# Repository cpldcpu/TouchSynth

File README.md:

# TouchSynth

A small MCU-controlled analog monophonic synthesizer on a 100 × 100 mm, 4-layer PCB. It has no
potentiometers and no mechanical switches: 13 capacitive touch keys plus SHIFT / − / + play and edit it, and
16 LEDs show the settings. A CH32V003 (or CH32V002 / V006) generates the oscillator timing and four
PWM control voltages for a discrete analog voice:

- **DCO:** a TL072 integrator reset by the MCU timer. The charge current tracks pitch, so the saw amplitude
  stays flat. Saw, variable-width pulse, sub-oscillator and noise.
- **VCF:** a 24 dB/oct transistor ladder (BC847BS) with an expo converter and resonance up to self-oscillation.
- **VCA:** a differential-pair VCA. An 8-bit R-2R trim DAC nulls the CV feedthrough ("thump").
- **Line out,** an audio loopback into the MCU ADC (for calibration and tests), and an optional MIDI in.

All assembled parts are JLCPCB **Basic** or **Promotional Extended** parts: 40 BOM lines, 196 placements,
about USD 3.65 of parts per board at list price. The MCU, headers and MIDI parts are hand-soldered.

**Status (2026-10-18):** board 1 (rev 0.1, CH32V006) is built and brought up. It passes the bring-up steps
and functional tests T1, T2 and T4–T12 (noise marginal at about −55 dB); T3 (touch scan rate) and T14 (MIDI)
have not been measured. The results are in the
[design report](docs/report/touchsynth_report.pdf), section 10. Firmware 0.1 runs on the board, including
multitrack demo pieces and percussion presets. Calibration storage in flash is still open.

The `polyphonic_exp` branch experiments with extensions. So far it turns the pulse output into a PWM DAC
(CH32V006) for digital voices through the analog filter and VCA, starting with a modal timpani, the *kettle*
([kettle_model.mp3](docs/audio/pieces/kettle_model.mp3); report, section 10.5).

Design: cpldcpu & Claude Opus 5.5.

## Hear it

Recorded from board 1's line out. The synth is monophonic, so the multitrack pieces were played one part at a
time and mixed:

| Piece | Board 1 | Model |
|---|---|---|
| *TouchSynth Demo*, original, 7 parts (drums, acid bass, arp, lead, pad) | [demo_hw](docs/audio/demo/touchsynth_demo_hw.mp3) | [demo_model](docs/audio/demo/touchsynth_demo_model.mp3) |
| Purcell, *Queen Mary's March*: 4 trumpets, bass, timpani (modal synthesis on the PWM DAC) | [march_hw](docs/audio/pieces/march_hw.mp3) | [march_model](docs/audio/pieces/march_model.mp3) |
| Bach, Toccata BWV 565, mm. 1–30: 9 organ voices | [toccata_hw](docs/audio/pieces/toccata_hw.mp3) | [toccata_model](docs/audio/pieces/toccata_model.mp3) |
| *Aerosphere*, original space-synth piece, 8 parts | [aero_hw](docs/audio/pieces/aero_hw.mp3) | [aero_model](docs/audio/pieces/aero_model.mp3) |
| Suite: Aerosphere intro into the Toccata | [suite_hw](docs/audio/pieces/suite_hw.mp3) | [suite_model](docs/audio/pieces/suite_model.mp3) |

The three built-in demo tunes (SHIFT + C' on the board), recorded from board 1:
[acid](docs/audio/hw_board1/tune_acid.mp3), [prelude](docs/audio/hw_board1/tune_prelude.mp3) (Bach BWV 846) and
[ode](docs/audio/hw_board1/tune_ode.mp3) (Beethoven). Also from the board: a
[waveform tour](docs/audio/hw_board1/waveforms.mp3) and a [scale on the self-oscillating filter](docs/audio/hw_board1/selfosc_scale.mp3).
The behavioural model renders every single feature (waveforms, filter, envelopes, glide, …) in
[docs/audio/features/](docs/audio/features/). [docs/README.md](docs/README.md) lists all audio files.

## Documents

| Document | Content |
|---|---|
| [docs/report/touchsynth_report.pdf](docs/report/touchsynth_report.pdf) | **design report**: requirements, architecture, circuits, simulations, PCB, BOM, firmware, demo tunes and instruments, V&V with the board 1 results |
| [docs/README.md](docs/README.md) | index of everything in `docs/`: documents, figures, result data, audio |
| [docs/spec.md](docs/spec.md) | specification and design decisions (some pre-layout details are outdated; the report is current) |
| [docs/sim_report.md](docs/sim_report.md) | simulation report S1–S7 and the behavioural model |
| [docs/verification_plan.md](docs/verification_plan.md) | bring-up, functional tests, calibration and validation, board 1 results |
| [docs/touchsynth_schematic.pdf](docs/touchsynth_schematic.pdf) | schematic (7 sheets) |
| [firmware/touchsynth/README.md](firmware/touchsynth/README.md) | firmware build, playing instructions and test console |
| [hw/README.md](hw/README.md) | schematic generator scripts |

## Repository layout

```
docs/        report (LaTeX), spec, simulation report, V&V plan, figures, audio examples, result CSVs
sim/         ngspice simulations S1–S7 (one folder per block), shared netlists and models, behavioural model
hw/          design.py (single source of truth) -> KiCad schematic, PCB, routing and fab outputs
  touchsynth/  KiCad 10 project (generated; edit the Python sources, not the KiCad files)
firmware/    touchsynth/ firmware 0.1, ch32fun (git submodule)
parts/       JLCPCB Basic / Promotional Extended part lists
tools/       bench tools: hardware tests, scope recording, multitrack mixing, figures; Freerouting jar (not in git)
```

## Flow

Every stage is generated by scripts from [hw/design.py](hw/design.py), which holds the parts, values, LCSC
numbers and nets.

```
simulate      sim/s*/s*.py                 ngspice-42 in WSL -> docs/results/*.csv, docs/figures/*.png
model         sim/behav/validate.py        behavioural model vs. ngspice
              sim/behav/examples.py        audio examples + spectrograms
schematic     hw/gen_sch2.py               -> hw/touchsynth/*.kicad_sch
              hw/check_netlist.py          KiCad netlist == design.py
              hw/check_sim.py              design.py == simulation netlists
PCB           hw/gen_pcb.py [--route]      placement, silkscreen art, planes, Freerouting + GND stitching
              hw/gen_pcb.py --finish       post-route clean-up (islands, leftovers via the A* router)
fab           hw/fab.py                    gerbers, drill, BOM and CPL -> hw/touchsynth/production/
report        docs/report/gen_tables.py    then: latexmk -pdf touchsynth_report.tex (WSL)
firmware      firmware/touchsynth/gen_tables.py, check_pins.py, make
tunes         sim/behav/tunes.py, pieces.py    demo tunes, multitrack pieces and presets (-> firmware tables)
bench         tools/hwtest.py              functional tests over the SWIO console -> docs/results/hw_board1*
              tools/hw_figures.py          board 1 figures for the report
              tools/record_parts.sh        record one multitrack part per take with the scope (on the lab PC)
              tools/mix_parts.py, suite.py align, clock-correct and mix the takes -> docs/audio/
```

The bench tools need the lab setup (the PC with the programmer, the scope address) in `tools/lab.conf`: copy
[tools/lab.conf.example](tools/lab.conf.example) and edit it; `lab.conf` is not in git.

`gen_pcb.py` needs KiCad's bundled Python (`pcbnew`) and Java 17 for Freerouting 1.9.0. The hw scripts find KiCad 10
in its standard install folder, or in `KICAD_DIR` if set. The other Python
scripts use a normal Python 3 with numpy and matplotlib. ngspice, LaTeX and the RISC-V toolchain run in WSL.

## Key numbers

| | |
|---|---|
| Supply | 9–12 V DC, about 31 mA (simulated); board 1: 25 mA, MCU running, LEDs off |
| Pitch range | C1 … C8, saw amplitude flat within ±2.2 % |
| Filter | 20 Hz … 20 kHz cutoff, −23 dB/oct, self-oscillation |
| VCA | 121 dB off-attenuation, thump < 0.6 mV after trim |
| Output | about 1.2 Vpp line level, AC-coupled |
| Control | 4 × 12-bit CV (10-bit PWM at 46.9 kHz + 2-bit dither), 1 kHz envelope / LFO rate |
| Touch | 16 pads via 2 × CD4051, 1.4 kHz scan |
| PCB | 100 × 100 mm, 4 layers (signal / GND / split power / signal), 242 parts, 166 nets |

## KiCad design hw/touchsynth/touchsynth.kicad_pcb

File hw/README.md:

# TouchSynth hardware (KiCad 10)

Everything here is generated from Python; edit the sources, not the `.kicad_sch` files.

| File | Role |
|---|---|
| `design.py` | single source of truth: parts (value, footprint, LCSC, sim name), nets, sheets, groups |
| `lcsc.py` | picks JLCPCB basic / promotional parts for passives (voltage rating >= 2x working voltage) |
| `layouts.py` | hand-drawn sheet layouts (placement + wires) |
| `draw.py` | drawing layer: geometric connectivity, auto-labels for split nets, short detection, junctions |
| `gen_sch2.py` | writes the schematic (`touchsynth/*.kicad_sch`) — **use this one** |
| `gen_sch.py` | v1 generator (label-only layout); its writer functions are reused by v2 |
| `check_netlist.py` | exports the KiCad netlist and compares it with `design.py` |
| `check_sim.py` | compares the design with the ngspice netlists (S6 + S7) |
| `touchsynth/TouchSynth.pretty` | touch-key footprints (copper under solder mask) |

```
python gen_sch2.py && kicad-cli sch erc touchsynth/touchsynth.kicad_sch && python check_netlist.py && python check_sim.py
```

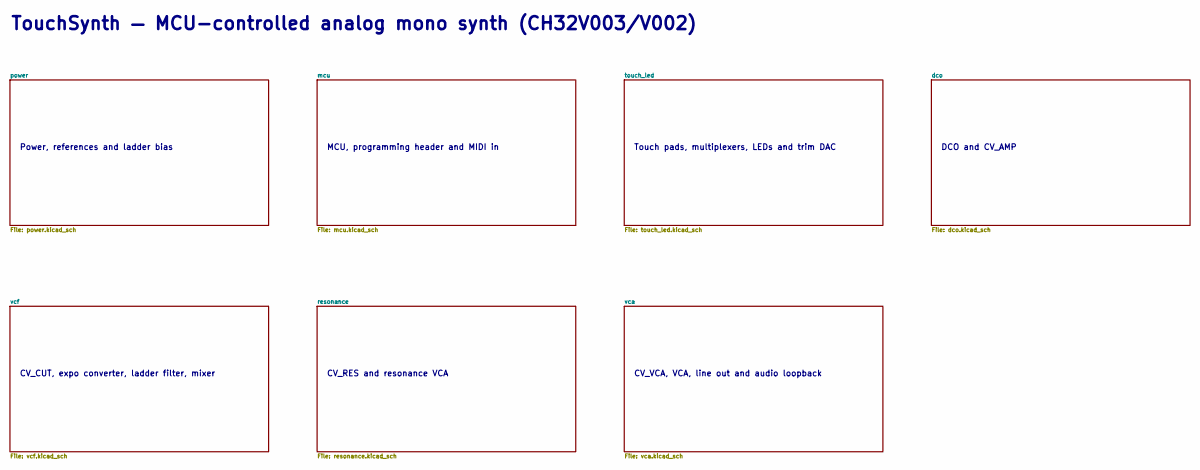
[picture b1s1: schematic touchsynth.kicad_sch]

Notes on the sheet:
Power, references and ladder bias
MCU, programming header and MIDI in
Touch pads, multiplexers, LEDs and trim DAC
DCO and CV_AMP
CV_CUT, expo converter, ladder filter, mixer
CV_RES and resonance VCA
CV_VCA, VCA, line out and audio loopback
TouchSynth — MCU-controlled analog mono synth (CH32V003/V002)

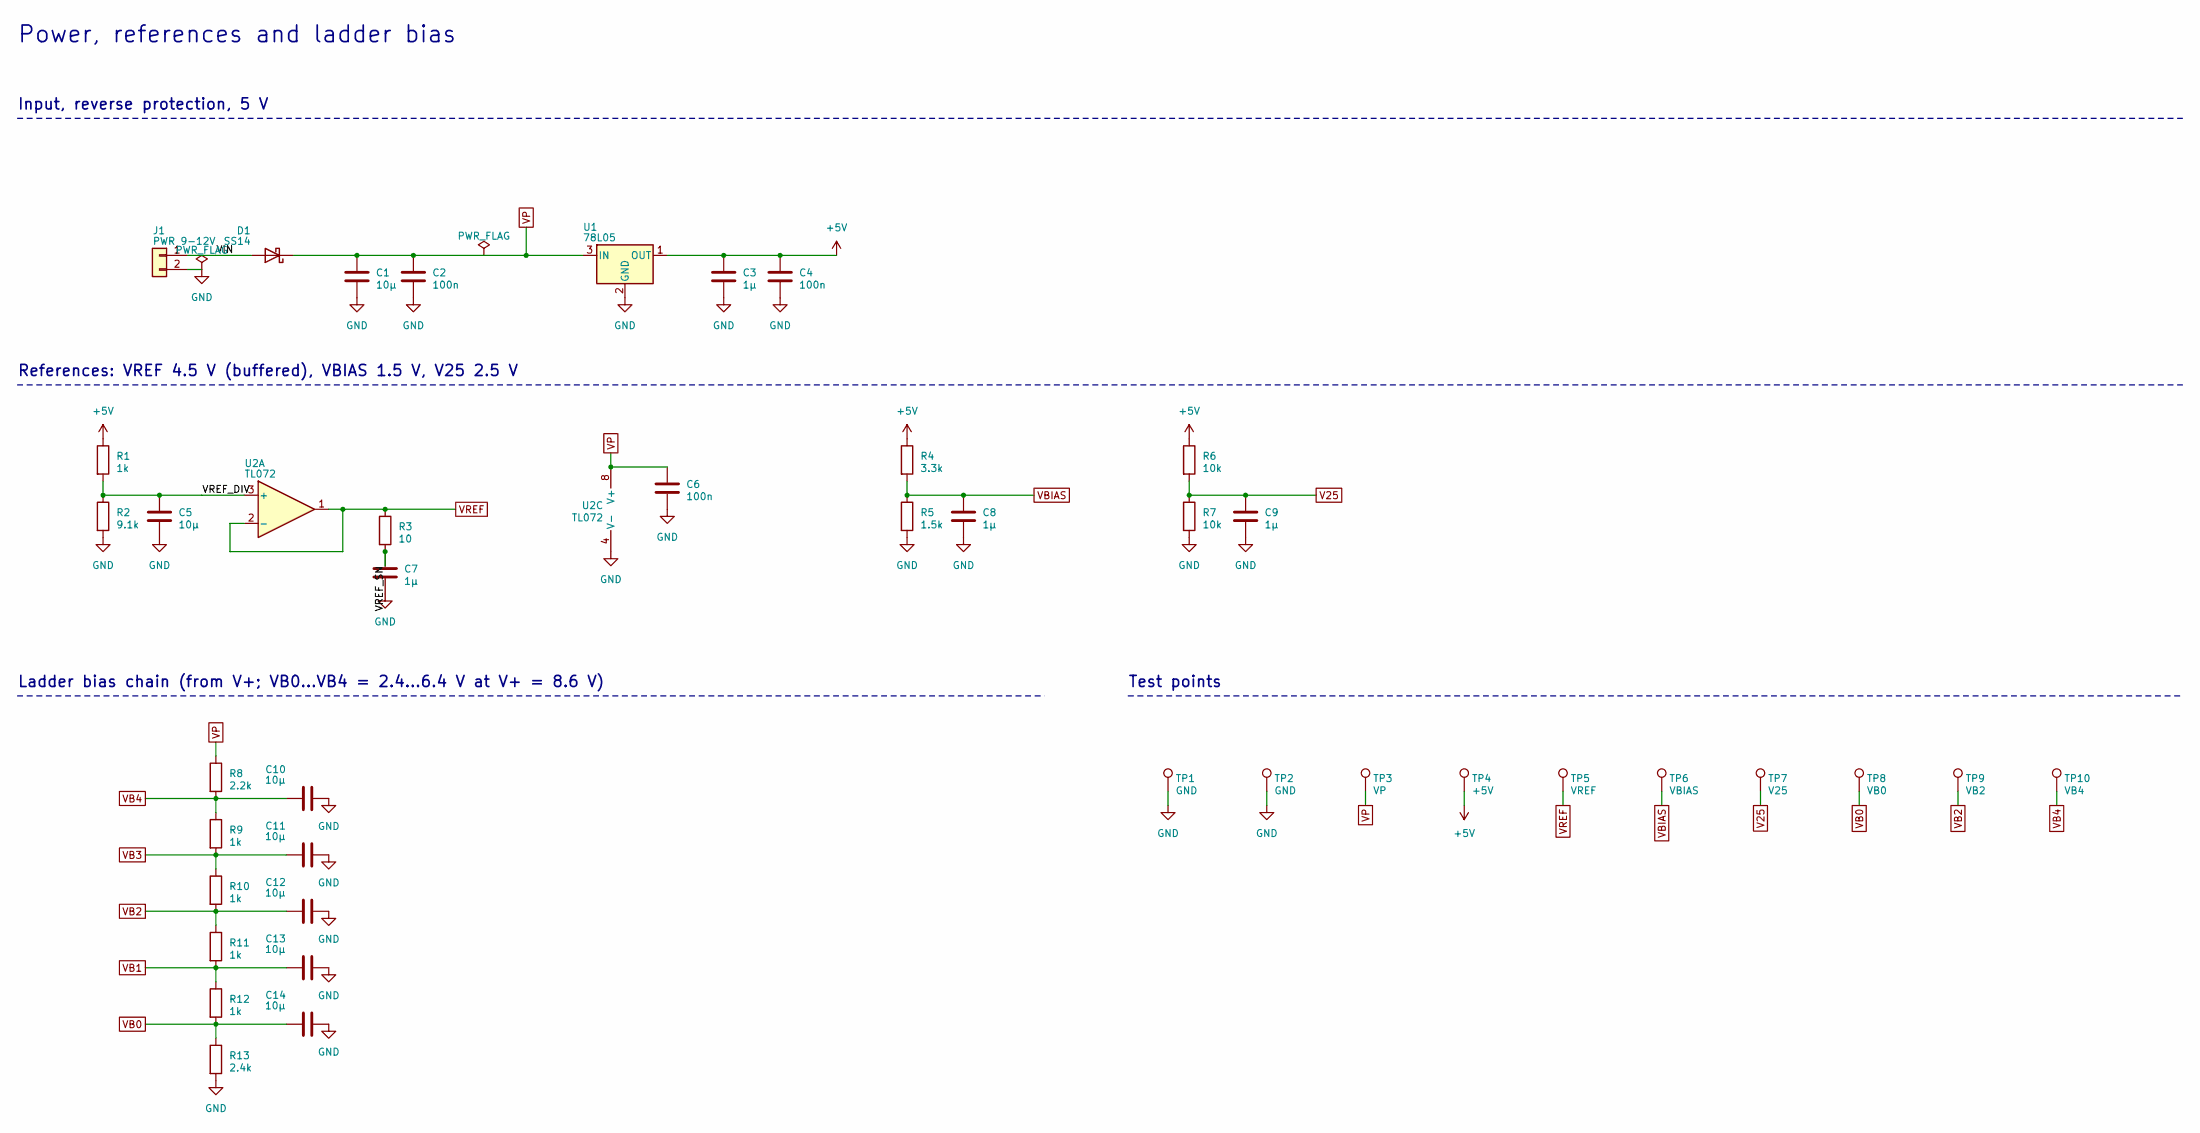
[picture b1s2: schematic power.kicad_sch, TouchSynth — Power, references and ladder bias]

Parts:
C1, C10, C11, C12, C13: 10µ; C_0603_1608Metric; LCSC C96446
C2, C4, C6: 100n; C_0603_1608Metric; LCSC C14663
C3, C7, C8, C9: 1µ; C_0603_1608Metric; LCSC C15849
C5, C14: 10µ; C_0603_1608Metric; LCSC C19702
D1: SS14; D_SMA; LCSC C2480
J1: PWR 9-12V; PinHeader_1x02_P2.54mm_Vertical
R1, R9, R10, R11, R12: 1k; R_0603_1608Metric; LCSC C21190
R2: 9.1k; R_0603_1608Metric; LCSC C23260
R3: 10; R_0603_1608Metric; LCSC C22859
R4: 3.3k; R_0603_1608Metric; LCSC C22978
R5: 1.5k; R_0603_1608Metric; LCSC C22843
R6, R7: 10k; R_0603_1608Metric; LCSC C25804
R8: 2.2k; R_0603_1608Metric; LCSC C4190
R13: 2.4k; R_0603_1608Metric; LCSC C22940
TP1, TP2: GND; PinHeader_1x01_P2.54mm_Vertical
TP3: VP; TestPoint_Pad_D1.0mm
TP4: +5V; TestPoint_Pad_D1.0mm
TP5: VREF; TestPoint_Pad_D1.0mm
TP6: VBIAS; TestPoint_Pad_D1.0mm
TP7: V25; TestPoint_Pad_D1.0mm
TP8: VB0; TestPoint_Pad_D1.0mm
TP9: VB2; TestPoint_Pad_D1.0mm
TP10: VB4; TestPoint_Pad_D1.0mm
U1: 78L05; SOT-89-3; LCSC C71136
U2: TL072; SOIC-8_3.9x4.9mm_P1.27mm; LCSC C6961

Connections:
+5V: C3.1, C4.1, R1.1, R4.1, R6.1, TP4.1, U1.1 (OUT); also elsewhere on the board
/power/VIN: D1.2 (A), J1.1
/power/VREF_DIV: C5.1, R1.2, R2.1, U2.3 (+)
/power/VREF_SN: C7.1, R3.2
GND: C1.2, C2.2, C3.2, C4.2, C5.2, C6.2, C7.2, C8.2, C9.2, C10.2, C11.2, C12.2, C13.2, C14.2, J1.2, R2.2, R5.2, R7.2, R13.2, TP1.1, TP2.1, U1.2 (GND), U2.4 (V-); also elsewhere on the board
V25: C9.1, R6.2, R7.1, TP7.1; also elsewhere on the board
VB0: C14.1, R12.2, R13.1, TP8.1; also elsewhere on the board
VB1: C13.1, R11.2, R12.1; also elsewhere on the board
VB2: C12.1, R10.2, R11.1, TP9.1; also elsewhere on the board
VB3: C11.1, R9.2, R10.1; also elsewhere on the board
VB4: C10.1, R8.2, R9.1, TP10.1; also elsewhere on the board
VBIAS: C8.1, R4.2, R5.1, TP6.1; also elsewhere on the board
VP: C1.1, C2.1, C6.1, D1.1 (K), R8.1, TP3.1, U1.3 (IN), U2.8 (V+); also elsewhere on the board
VREF: R3.1, TP5.1, U2.1, U2.2 (-); also elsewhere on the board

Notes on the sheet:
Power, references and ladder bias
Input, reverse protection, 5 V
References: VREF 4.5 V (buffered), VBIAS 1.5 V, V25 2.5 V
Ladder bias chain (from V+; VB0...VB4 = 2.4...6.4 V at V+ = 8.6 V)
Test points

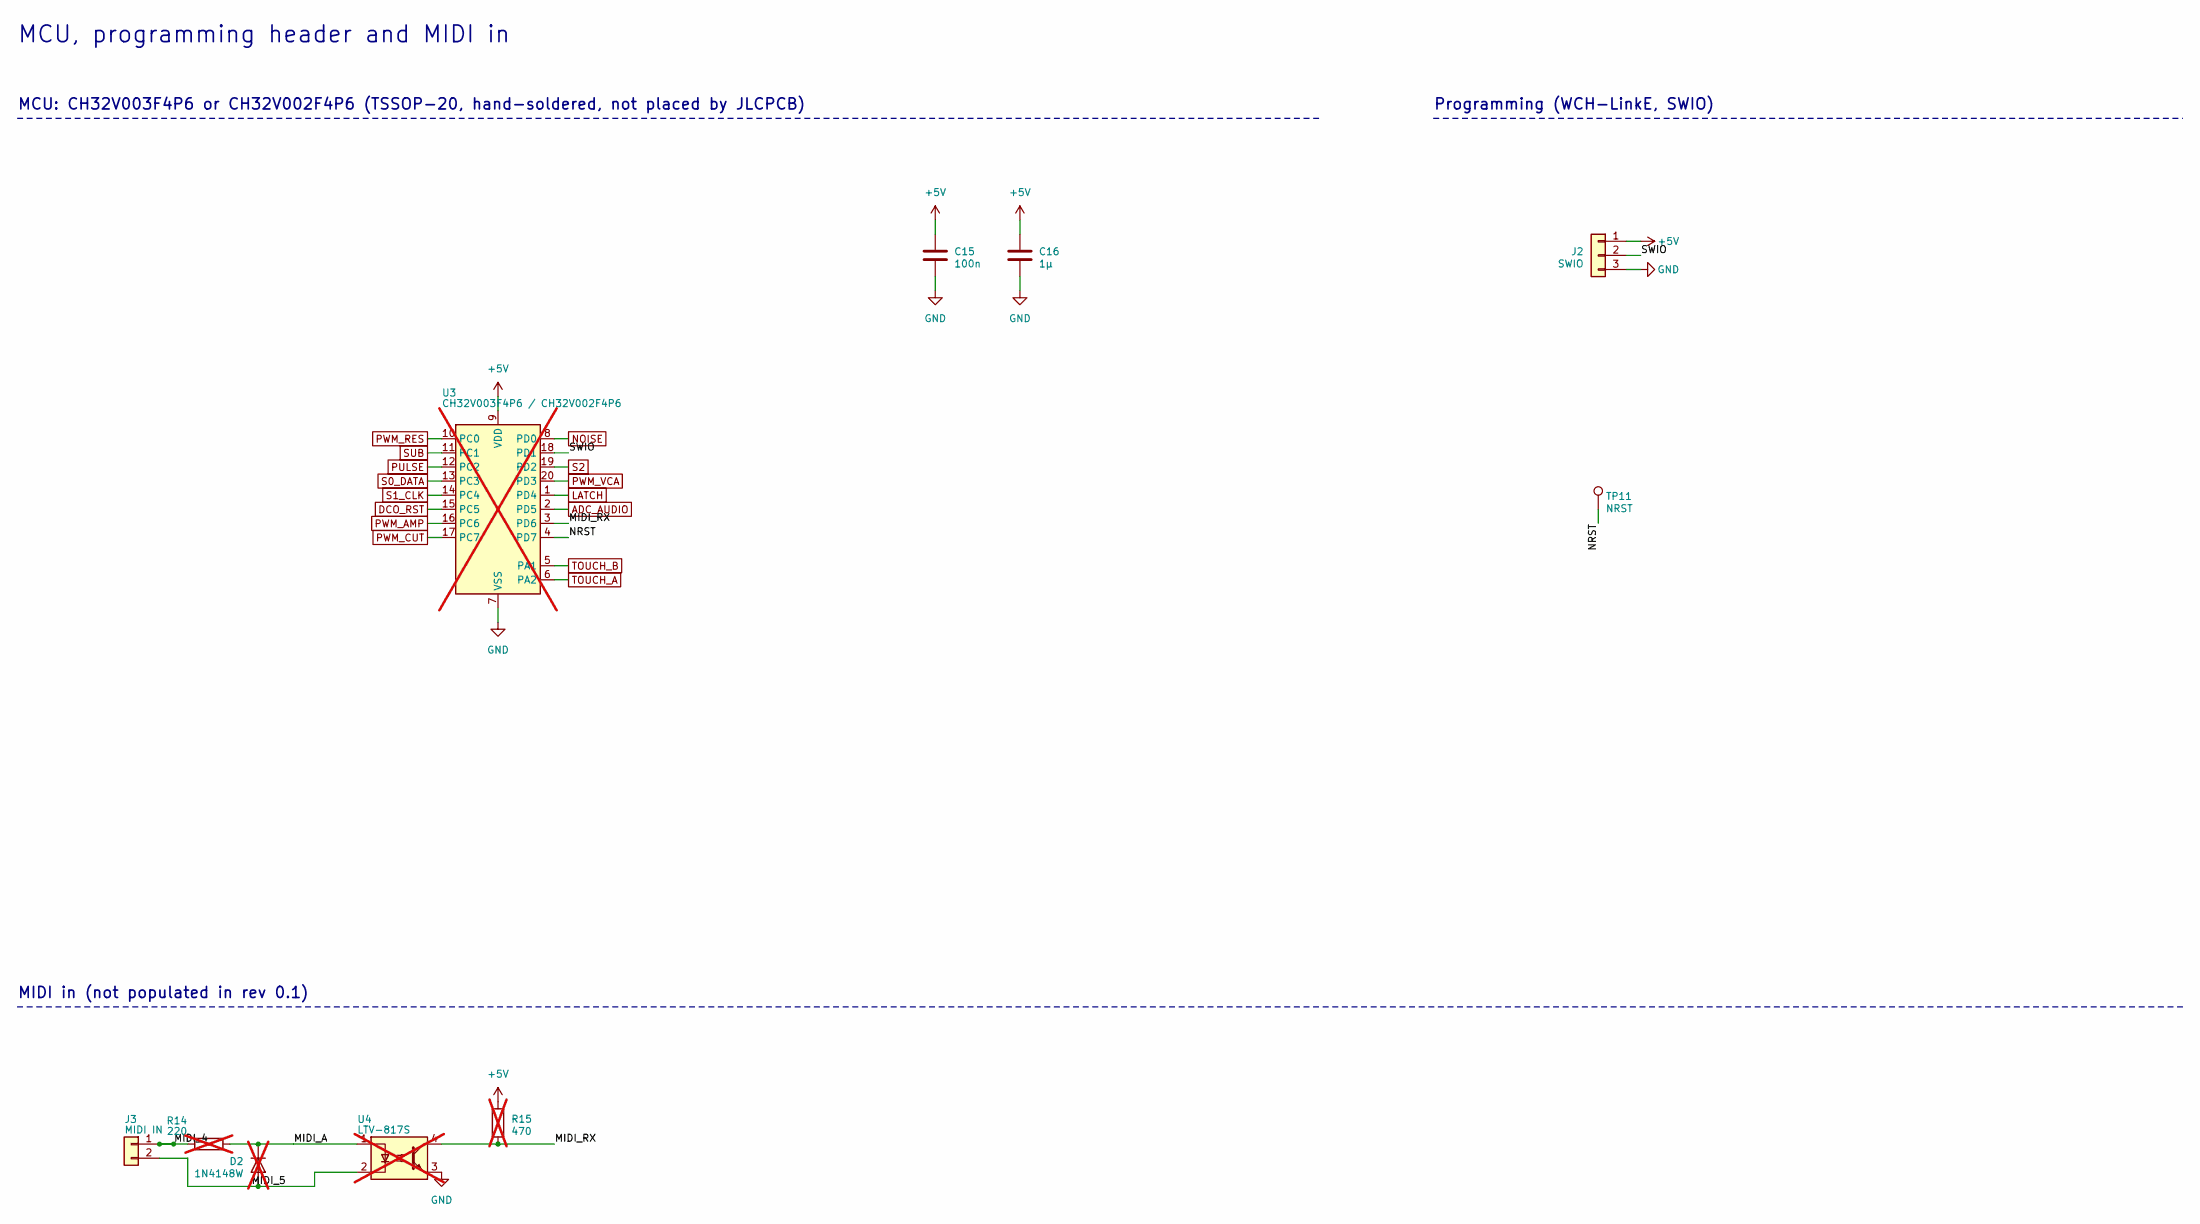
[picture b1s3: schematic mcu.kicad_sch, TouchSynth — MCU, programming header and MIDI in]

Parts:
C15: 100n; C_0603_1608Metric; LCSC C14663
C16: 1µ; C_0603_1608Metric; LCSC C15849
D2: 1N4148W; D_SOD-123; LCSC C81598; not fitted
J2: SWIO; PinHeader_1x03_P2.54mm_Vertical
J3: MIDI IN; PinHeader_1x02_P2.54mm_Vertical
R14: 220; R_0603_1608Metric; LCSC C22962; not fitted
R15: 470; R_0603_1608Metric; LCSC C23179; not fitted
TP11: NRST; TestPoint_Pad_D1.0mm
U3: CH32V003F4P6 / CH32V002F4P6; TSSOP-20_4.4x6.5mm_P0.65mm; not fitted
U4: LTV-817S; SMDIP-4_W9.53mm; LCSC C109227; not fitted

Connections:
+5V: C15.1, C16.1, J2.1, R15.1, U3.9 (VDD); also elsewhere on the board
/mcu/MIDI_4: J3.1, R14.1
/mcu/MIDI_5: D2.2 (A), J3.2, U4.2
/mcu/MIDI_A: D2.1 (K), R14.2, U4.1
/mcu/MIDI_RX: R15.2, U3.3 (PD6), U4.4
/mcu/NRST: TP11.1, U3.4 (PD7)
/mcu/SWIO: J2.2, U3.18 (PD1)
ADC_AUDIO: U3.2 (PD5); also elsewhere on the board
DCO_RST: U3.15 (PC5); also elsewhere on the board
GND: C15.2, C16.2, J2.3, U3.7 (VSS), U4.3; also elsewhere on the board
LATCH: U3.1 (PD4); also elsewhere on the board
NOISE: U3.8 (PD0); also elsewhere on the board
PULSE: U3.12 (PC2); also elsewhere on the board
PWM_AMP: U3.16 (PC6); also elsewhere on the board
PWM_CUT: U3.17 (PC7); also elsewhere on the board
PWM_RES: U3.10 (PC0); also elsewhere on the board
PWM_VCA: U3.20 (PD3); also elsewhere on the board
S0_DATA: U3.13 (PC3); also elsewhere on the board
S1_CLK: U3.14 (PC4); also elsewhere on the board
S2: U3.19 (PD2); also elsewhere on the board
SUB: U3.11 (PC1); also elsewhere on the board
TOUCH_A: U3.6 (PA2); also elsewhere on the board
TOUCH_B: U3.5 (PA1); also elsewhere on the board

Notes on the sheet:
MCU, programming header and MIDI in
MCU: CH32V003F4P6 or CH32V002F4P6 (TSSOP-20, hand-soldered, not placed by JLCPCB)
Programming (WCH-LinkE, SWIO)
MIDI in (not populated in rev 0.1)

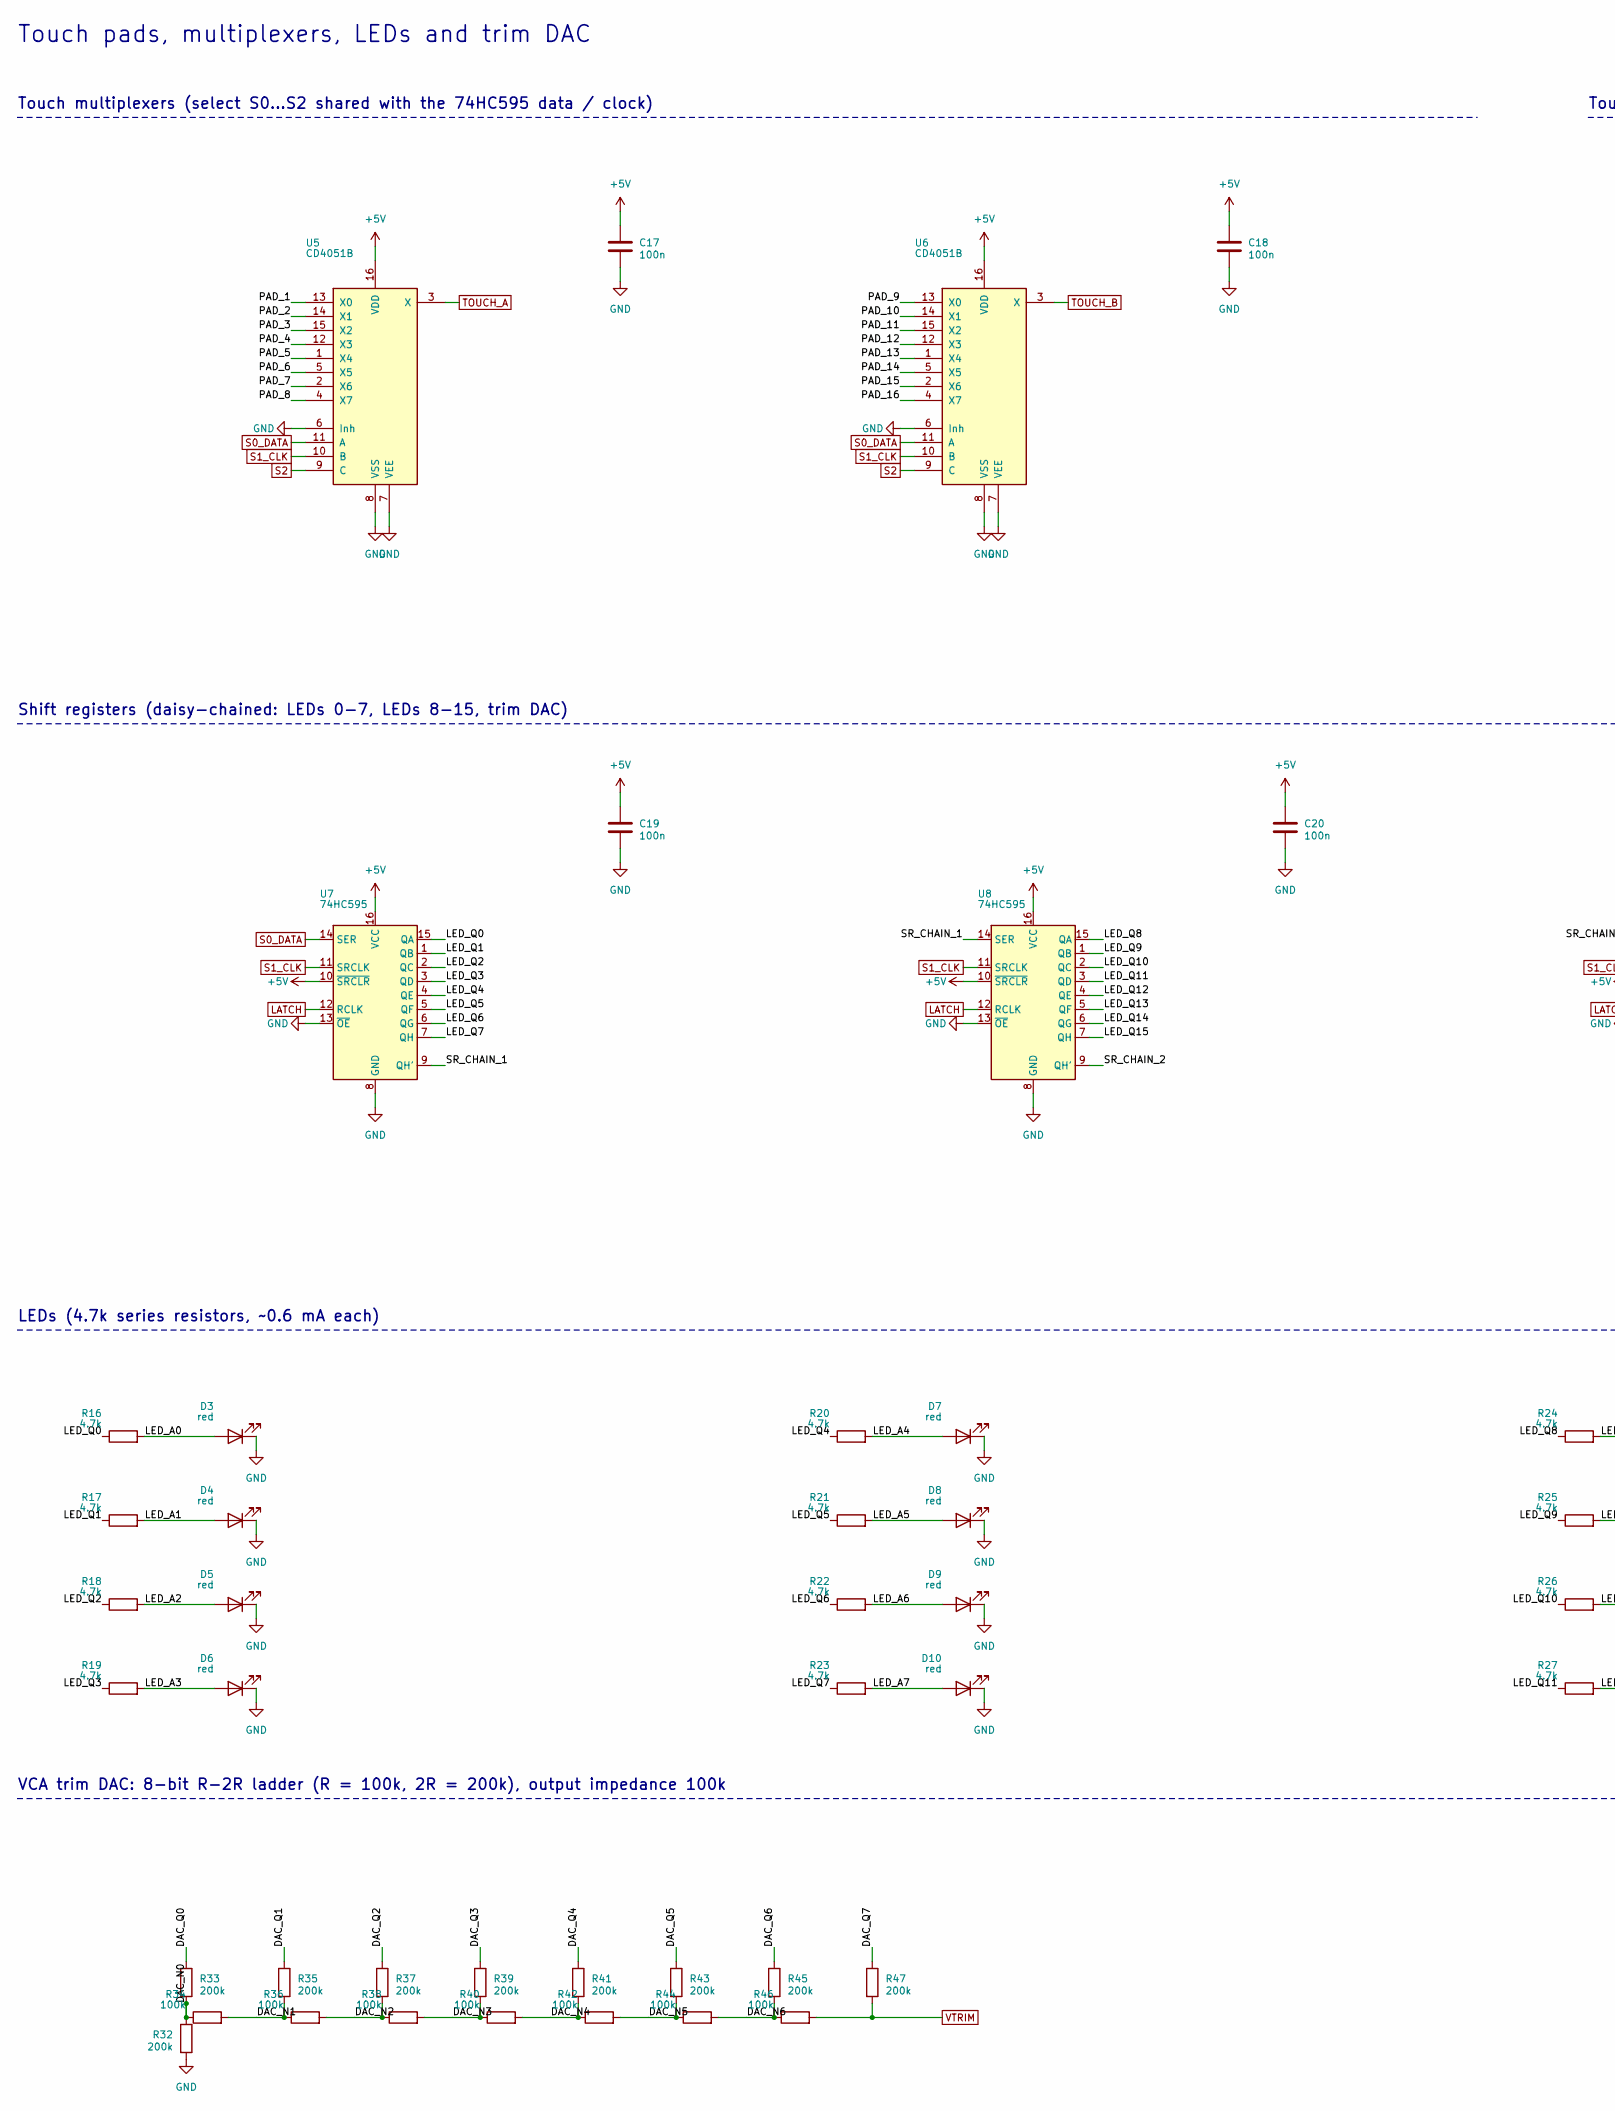
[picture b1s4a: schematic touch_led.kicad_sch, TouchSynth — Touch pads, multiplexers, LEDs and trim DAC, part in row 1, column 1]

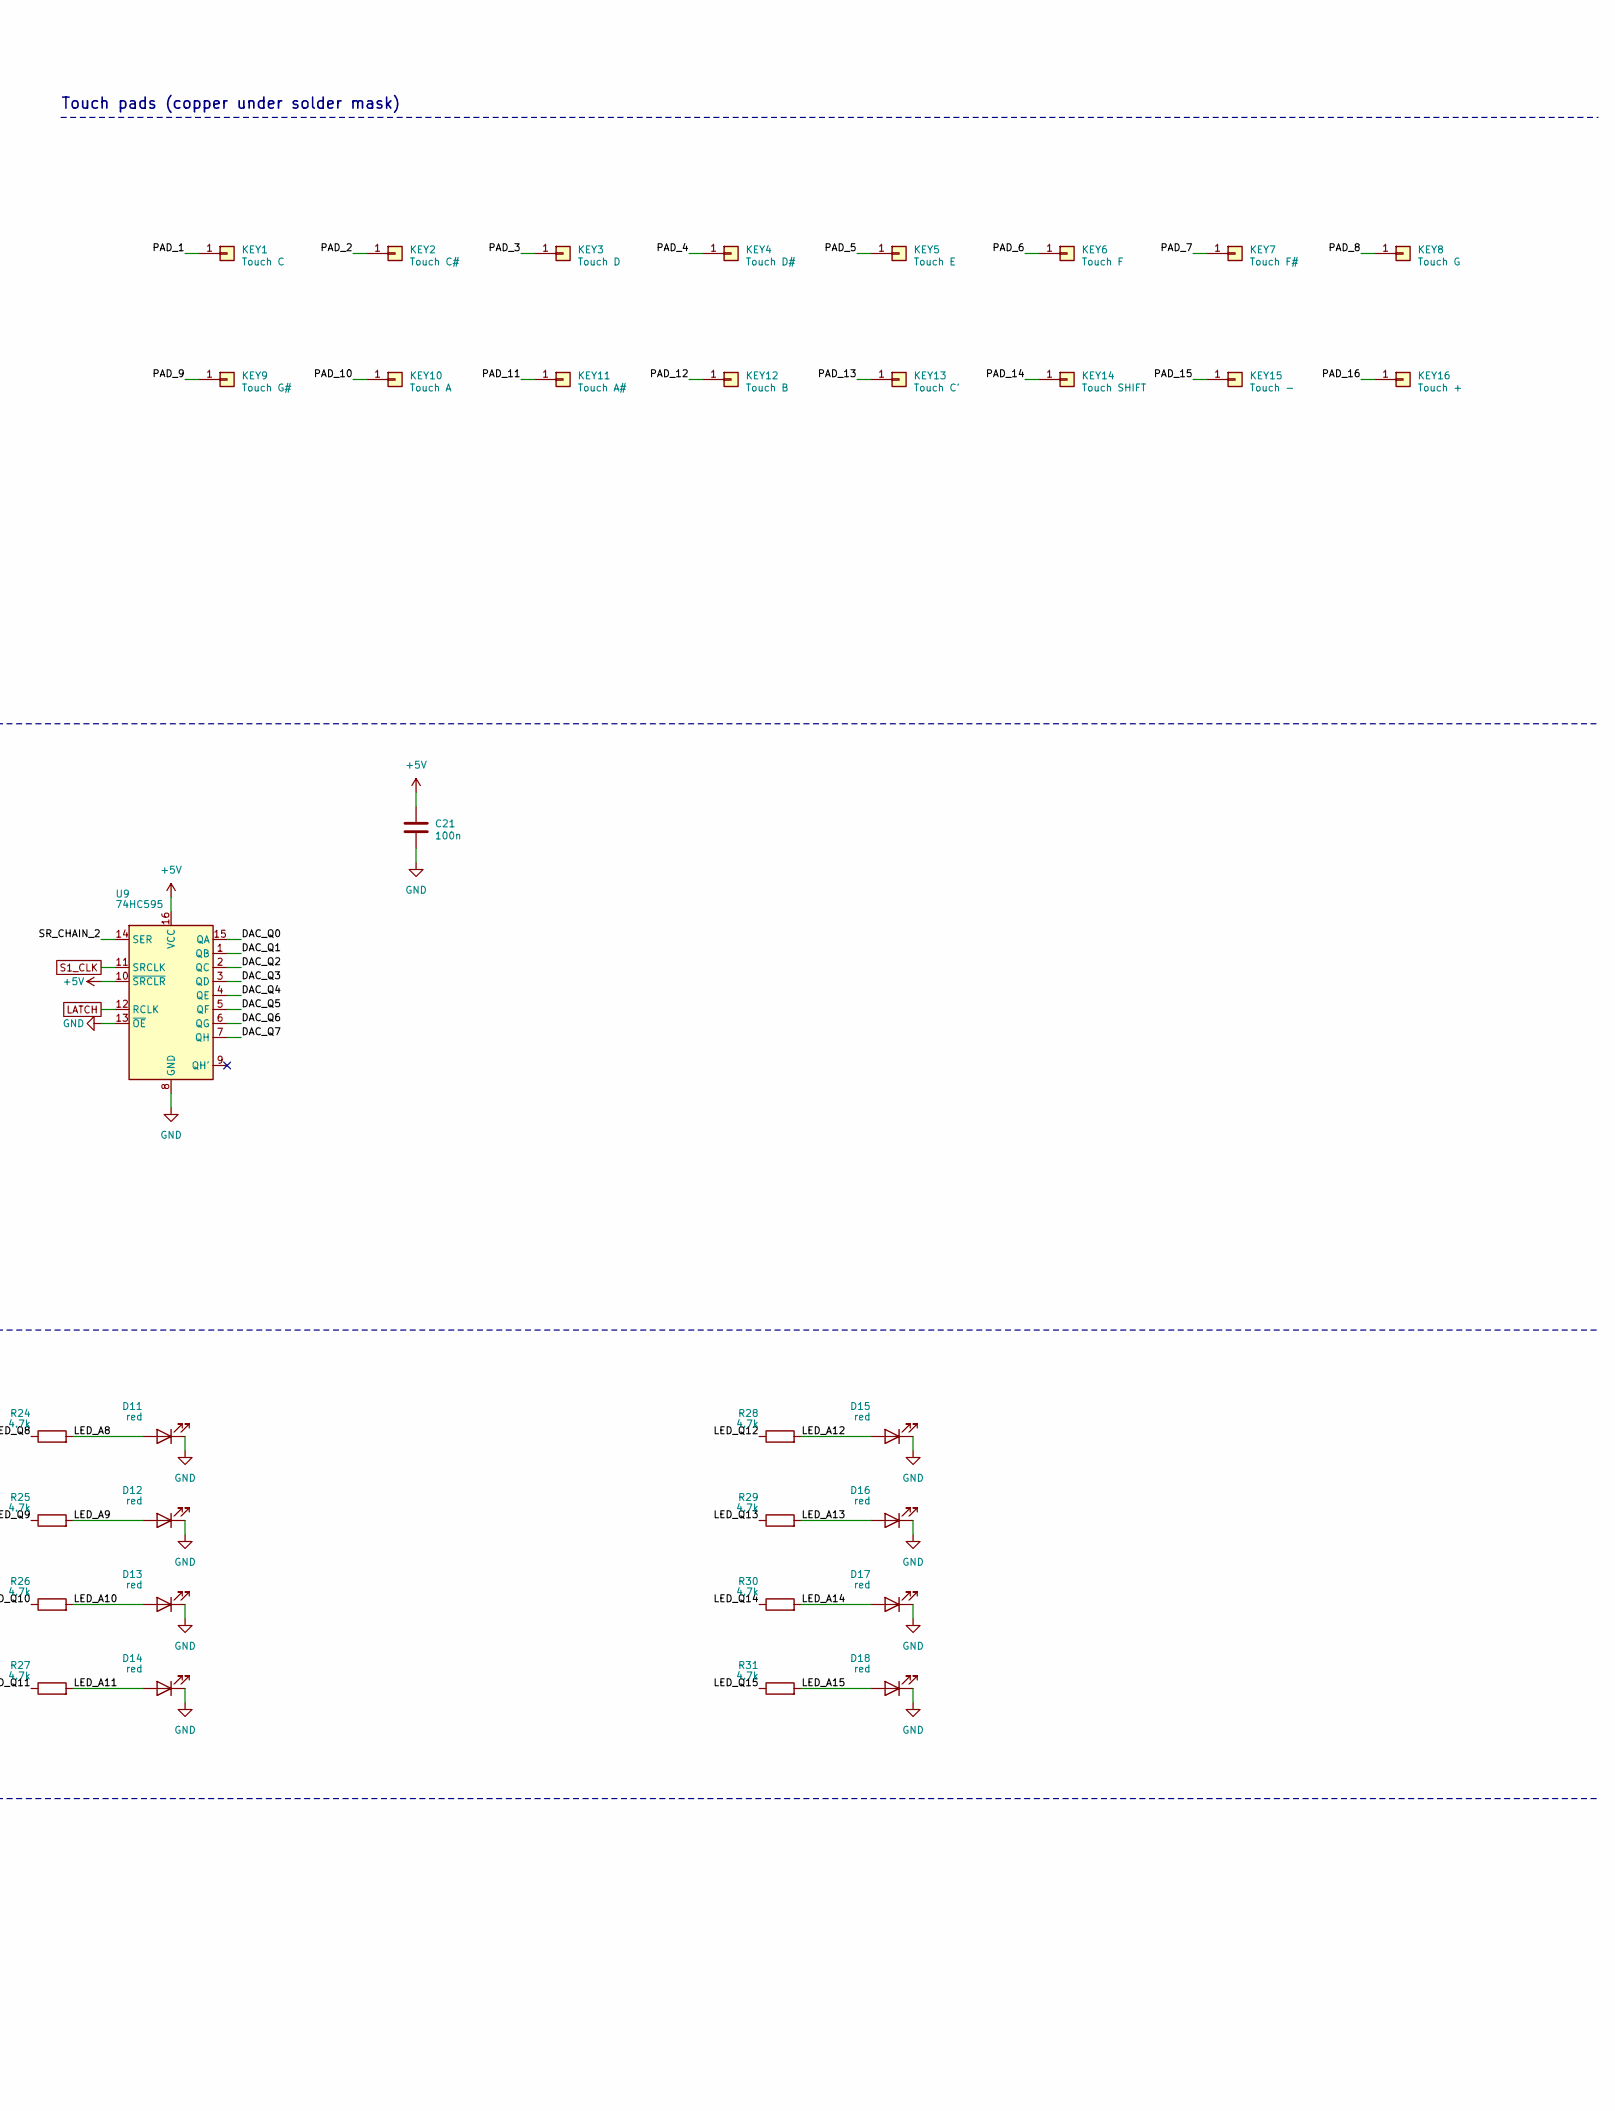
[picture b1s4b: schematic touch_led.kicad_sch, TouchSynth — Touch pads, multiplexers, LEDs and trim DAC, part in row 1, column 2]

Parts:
C17, C18, C19, C20, C21: 100n; C_0603_1608Metric; LCSC C14663
D3, D4, D5, D6, D7, D8, D9, D10, D11, D12, D13, D14, D15, D16, D17, D18: red; LED_0603_1608Metric; LCSC C2286
KEY1: Touch C; TouchPad_White
KEY2: Touch C#; TouchPad_Black
KEY3: Touch D; TouchPad_White
KEY4: Touch D#; TouchPad_Black
KEY5: Touch E; TouchPad_White
KEY6: Touch F; TouchPad_White
KEY7: Touch F#; TouchPad_Black
KEY8: Touch G; TouchPad_White
KEY9: Touch G#; TouchPad_Black
KEY10: Touch A; TouchPad_White
KEY11: Touch A#; TouchPad_Black
KEY12: Touch B; TouchPad_White
KEY13: Touch C'; TouchPad_White
KEY14: Touch SHIFT; TouchPad_Func
KEY15: Touch -; TouchPad_Func
KEY16: Touch +; TouchPad_Func
R16, R17, R18, R19, R20, R21, R22, R23, R24, R25, R26, R27, R28, R29, R30, R31: 4.7k; R_0603_1608Metric; LCSC C23162
R32, R33, R35, R37, R39, R41, R43, R45, R47: 200k; R_0603_1608Metric; LCSC C25811
R34, R36, R38, R40, R42, R44, R46: 100k; R_0603_1608Metric; LCSC C25803
U5, U6: CD4051B; SOIC-16_3.9x9.9mm_P1.27mm; LCSC C21379
U7, U8, U9: 74HC595; SOIC-16_3.9x9.9mm_P1.27mm; LCSC C5947

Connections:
+5V: C17.1, C18.1, C19.1, C20.1, C21.1, U5.16 (VDD), U6.16 (VDD), U7.10 (~SRCLR), U7.16 (VCC), U8.10 (~SRCLR), U8.16 (VCC), U9.10 (~SRCLR), U9.16 (VCC); also elsewhere on the board
/touch_led/DAC_N0: R32.1, R33.2, R34.1
/touch_led/DAC_N1: R34.2, R35.2, R36.1
/touch_led/DAC_N2: R36.2, R37.2, R38.1
/touch_led/DAC_N3: R38.2, R39.2, R40.1
/touch_led/DAC_N4: R40.2, R41.2, R42.1
/touch_led/DAC_N5: R42.2, R43.2, R44.1
/touch_led/DAC_N6: R44.2, R45.2, R46.1
/touch_led/DAC_Q0: R33.1, U9.15 (QA)
/touch_led/DAC_Q1: R35.1, U9.1 (QB)
/touch_led/DAC_Q2: R37.1, U9.2 (QC)
/touch_led/DAC_Q3: R39.1, U9.3 (QD)
/touch_led/DAC_Q4: R41.1, U9.4 (QE)
/touch_led/DAC_Q5: R43.1, U9.5 (QF)
/touch_led/DAC_Q6: R45.1, U9.6 (QG)
/touch_led/DAC_Q7: R47.1, U9.7 (QH)
/touch_led/LED_A0: D3.2 (A), R16.2
/touch_led/LED_A1: D4.2 (A), R17.2
/touch_led/LED_A2: D5.2 (A), R18.2
/touch_led/LED_A3: D6.2 (A), R19.2
/touch_led/LED_A4: D7.2 (A), R20.2
/touch_led/LED_A5: D8.2 (A), R21.2
/touch_led/LED_A6: D9.2 (A), R22.2
/touch_led/LED_A7: D10.2 (A), R23.2
/touch_led/LED_A8: D11.2 (A), R24.2
/touch_led/LED_A9: D12.2 (A), R25.2
/touch_led/LED_A10: D13.2 (A), R26.2
/touch_led/LED_A11: D14.2 (A), R27.2
/touch_led/LED_A12: D15.2 (A), R28.2
/touch_led/LED_A13: D16.2 (A), R29.2
/touch_led/LED_A14: D17.2 (A), R30.2
/touch_led/LED_A15: D18.2 (A), R31.2
/touch_led/LED_Q0: R16.1, U7.15 (QA)
/touch_led/LED_Q1: R17.1, U7.1 (QB)
/touch_led/LED_Q2: R18.1, U7.2 (QC)
/touch_led/LED_Q3: R19.1, U7.3 (QD)
/touch_led/LED_Q4: R20.1, U7.4 (QE)
/touch_led/LED_Q5: R21.1, U7.5 (QF)
/touch_led/LED_Q6: R22.1, U7.6 (QG)
/touch_led/LED_Q7: R23.1, U7.7 (QH)
/touch_led/LED_Q8: R24.1, U8.15 (QA)
/touch_led/LED_Q9: R25.1, U8.1 (QB)
/touch_led/LED_Q10: R26.1, U8.2 (QC)
/touch_led/LED_Q11: R27.1, U8.3 (QD)
/touch_led/LED_Q12: R28.1, U8.4 (QE)
/touch_led/LED_Q13: R29.1, U8.5 (QF)
/touch_led/LED_Q14: R30.1, U8.6 (QG)
/touch_led/LED_Q15: R31.1, U8.7 (QH)
/touch_led/PAD_1: KEY1.1, U5.13 (X0)
/touch_led/PAD_2: KEY2.1, U5.14 (X1)
/touch_led/PAD_3: KEY3.1, U5.15 (X2)
/touch_led/PAD_4: KEY4.1, U5.12 (X3)
/touch_led/PAD_5: KEY5.1, U5.1 (X4)
/touch_led/PAD_6: KEY6.1, U5.5 (X5)
/touch_led/PAD_7: KEY7.1, U5.2 (X6)
/touch_led/PAD_8: KEY8.1, U5.4 (X7)
/touch_led/PAD_9: KEY9.1, U6.13 (X0)
/touch_led/PAD_10: KEY10.1, U6.14 (X1)
/touch_led/PAD_11: KEY11.1, U6.15 (X2)
/touch_led/PAD_12: KEY12.1, U6.12 (X3)
/touch_led/PAD_13: KEY13.1, U6.1 (X4)
/touch_led/PAD_14: KEY14.1, U6.5 (X5)
/touch_led/PAD_15: KEY15.1, U6.2 (X6)
/touch_led/PAD_16: KEY16.1, U6.4 (X7)
/touch_led/SR_CHAIN_1: U7.9 (QH'), U8.14 (SER)
/touch_led/SR_CHAIN_2: U8.9 (QH'), U9.14 (SER)
GND: C17.2, C18.2, C19.2, C20.2, C21.2, D3.1 (K), D4.1 (K), D5.1 (K), D6.1 (K), D7.1 (K), D8.1 (K), D9.1 (K), D10.1 (K), D11.1 (K), D12.1 (K), D13.1 (K), D14.1 (K), D15.1 (K), D16.1 (K), D17.1 (K), D18.1 (K), R32.2, U5.6 (Inh), U5.7 (VEE), U5.8 (VSS), U6.6 (Inh), U6.7 (VEE), U6.8 (VSS), U7.8 (GND), U7.13 (~OE), U8.8 (GND), U8.13 (~OE), U9.8 (GND), U9.13 (~OE); also elsewhere on the board
LATCH: U7.12 (RCLK), U8.12 (RCLK), U9.12 (RCLK); also elsewhere on the board
S0_DATA: U5.11 (A), U6.11 (A), U7.14 (SER); also elsewhere on the board
S1_CLK: U5.10 (B), U6.10 (B), U7.11 (SRCLK), U8.11 (SRCLK), U9.11 (SRCLK); also elsewhere on the board
S2: U5.9 (C), U6.9 (C); also elsewhere on the board
TOUCH_A: U5.3 (X); also elsewhere on the board
TOUCH_B: U6.3 (X); also elsewhere on the board
VTRIM: R46.2, R47.2; also elsewhere on the board

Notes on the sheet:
Touch pads, multiplexers, LEDs and trim DAC
Touch multiplexers (select S0...S2 shared with the 74HC595 data / clock)
Touch pads (copper under solder mask)
Shift registers (daisy-chained: LEDs 0-7, LEDs 8-15, trim DAC)
LEDs (4.7k series resistors, ~0.6 mA each)
VCA trim DAC: 8-bit R-2R ladder (R = 100k, 2R = 200k), output impedance 100k
